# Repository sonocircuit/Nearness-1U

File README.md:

# Nearness-1U

This is an adaption of [sarnesjo's nearness module](https://github.com/sarnesjo/nearness) in 1U Pulplogic format.

### Changes made:

- New layout and format. All parts fit on a single 2-layer PCB.
- Added a second input for the center position (50:50) instead of one.
- Added a 3pin link header to connect the outputs directly to an EXI[S]T module. Pluging a cable into the output jacks breaks the connection.

## Make your own

[Eagle files](https://github.com/sonoCircuits/Nearness-1U/tree/master/NEARNESS%201U%20EAGLE%20FILES)

[Octopart BOM](https://octopart.com/bom-tool/OzYDJwBg)

## Licence

Thanks to sarnesjo for sharing! Same licence applies.

[CC BY-SA 4.0](http://creativecommons.org/licenses/by-sa/4.0/)

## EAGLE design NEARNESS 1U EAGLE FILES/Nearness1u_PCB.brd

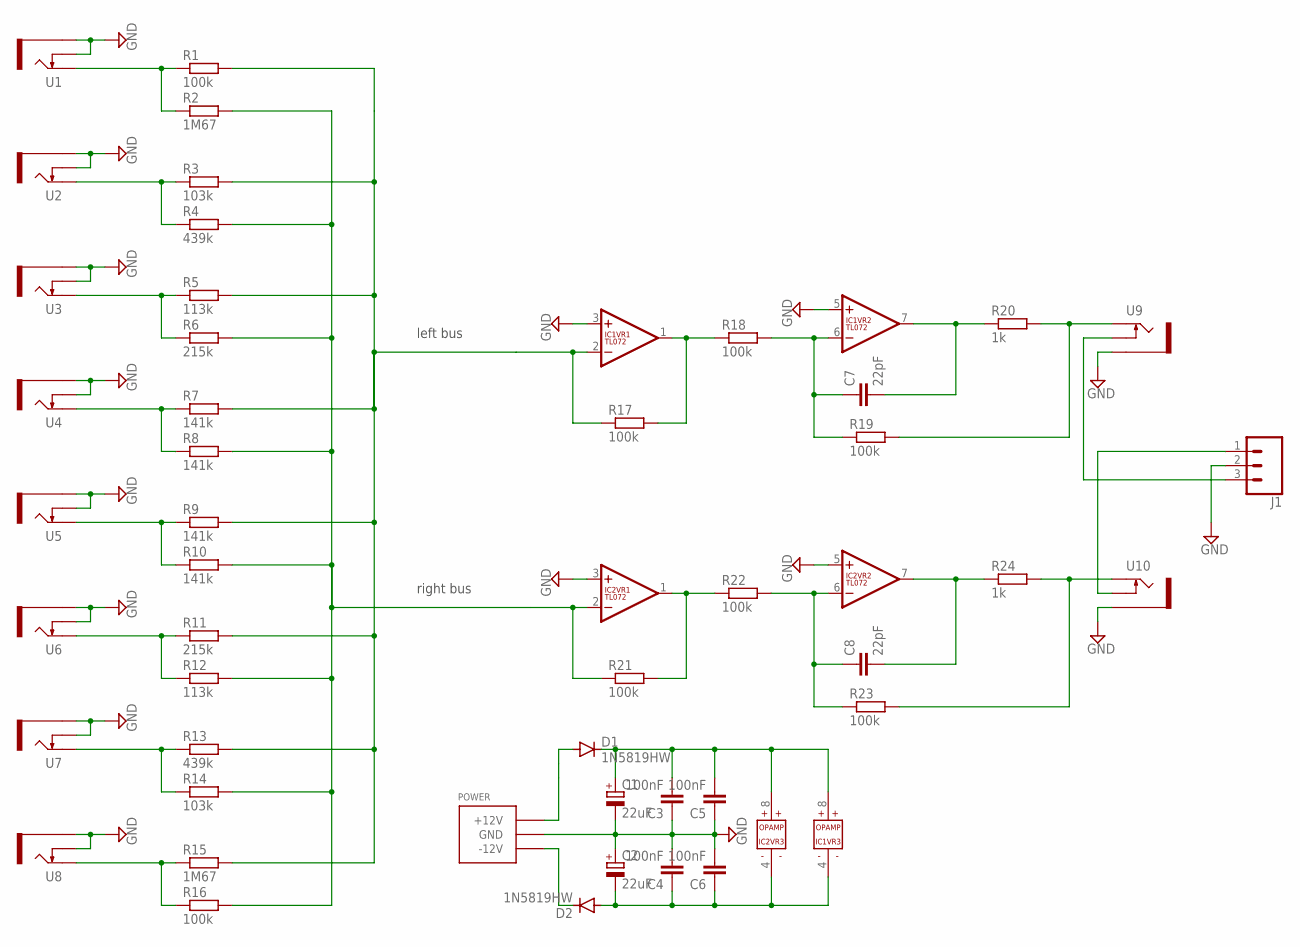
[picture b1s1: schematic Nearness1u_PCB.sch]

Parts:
C1, C2: 22uF; 153CLV-0405
C3, C4, C5, C6: 100nF; C0805
C7, C8: 22pF; C0805
D1, D2: 1N5819HW; SOD123
IC1, IC2: TL072; SO08
J1: CONN_03; 1X03
POWER: POWER_SIMPLE; 2X05_SMT_HEADER
R1, R16, R17, R18, R19, R21, R22, R23: 100k; R0805
R2, R15: 1M67; R0805
R3, R14: 103k; R0805
R4, R13: 439k; R0805
R5, R12: 113k; R0805
R6, R11: 215k; R0805
R7, R8, R9, R10: 141k; R0805
R20, R24: 1k; R0805
U1, U2, U3, U4, U5, U6, U7, U8, U9, U10: THONKICONNNEW; WQP-PJ301M-12_JACK

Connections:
GND: C1.-, C2.+, C3.1, C4.2, C5.1, C6.2, IC1.3 (+IN), IC1.5 (+IN), IC2.3 (+IN), IC2.5 (+IN), J1.2, POWER.3 (GND), POWER.4 (GND), POWER.5 (GND), POWER.6 (GND), POWER.7 (GND), POWER.8 (GND), U1.P$2_SWITCH (SWITCH), U1.P$3_SLEEVE (SLEEVE), U2.P$2_SWITCH (SWITCH), U2.P$3_SLEEVE (SLEEVE), U3.P$2_SWITCH (SWITCH), U3.P$3_SLEEVE (SLEEVE), U4.P$2_SWITCH (SWITCH), U4.P$3_SLEEVE (SLEEVE), U5.P$2_SWITCH (SWITCH), U5.P$3_SLEEVE (SLEEVE), U6.P$2_SWITCH (SWITCH), U6.P$3_SLEEVE (SLEEVE), U7.P$2_SWITCH (SWITCH), U7.P$3_SLEEVE (SLEEVE), U8.P$2_SWITCH (SWITCH), U8.P$3_SLEEVE (SLEEVE), U9.P$3_SLEEVE (SLEEVE), U10.P$3_SLEEVE (SLEEVE)
LEFT_BUS: IC1.2 (-IN), R1.2, R3.2, R5.2, R7.2, R9.2, R11.2, R13.2, R15.2, R17.1
unnamed: R1.1, R2.1, U1.P$1_TIP (TIP)
unnamed: IC2.1 (OUT), R21.2, R22.1
unnamed: C8.1, IC2.6 (-IN), R22.2, R23.1
unnamed: IC1.1 (OUT), R17.2, R18.1
unnamed: R3.1, R4.1, U2.P$1_TIP (TIP)
unnamed: C7.1, IC1.6 (-IN), R18.2, R19.1
unnamed: C7.2, IC1.7 (OUT), R20.1
unnamed: R5.1, R6.1, U3.P$1_TIP (TIP)
unnamed: C8.2, IC2.7 (OUT), R24.1
unnamed: R19.2, R20.2, U9.P$1_TIP (TIP)
unnamed: R7.1, R8.1, U4.P$1_TIP (TIP)
unnamed: R23.2, R24.2, U10.P$1_TIP (TIP)
unnamed: R9.1, R10.1, U5.P$1_TIP (TIP)
unnamed: D1.A, POWER.9 (+12V), POWER.10 (+12V)
unnamed: D2.C, POWER.1 (-12V), POWER.2 (-12V)
unnamed: R11.1, R12.1, U6.P$1_TIP (TIP)
unnamed: J1.3, U9.P$2_SWITCH (SWITCH)
unnamed: R13.1, R14.1, U7.P$1_TIP (TIP)
unnamed: J1.1, U10.P$2_SWITCH (SWITCH)
unnamed: R15.1, R16.1, U8.P$1_TIP (TIP)
RIGHT_BUS: IC2.2 (-IN), R2.2, R4.2, R6.2, R8.2, R10.2, R12.2, R14.2, R16.2, R21.1
V+: C1.+, C3.2, C5.2, D1.C, IC1.8 (V+), IC2.8 (V+)
V-: C2.-, C4.1, C6.1, D2.A, IC1.4 (V-), IC2.4 (V-)

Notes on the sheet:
left bus
right bus

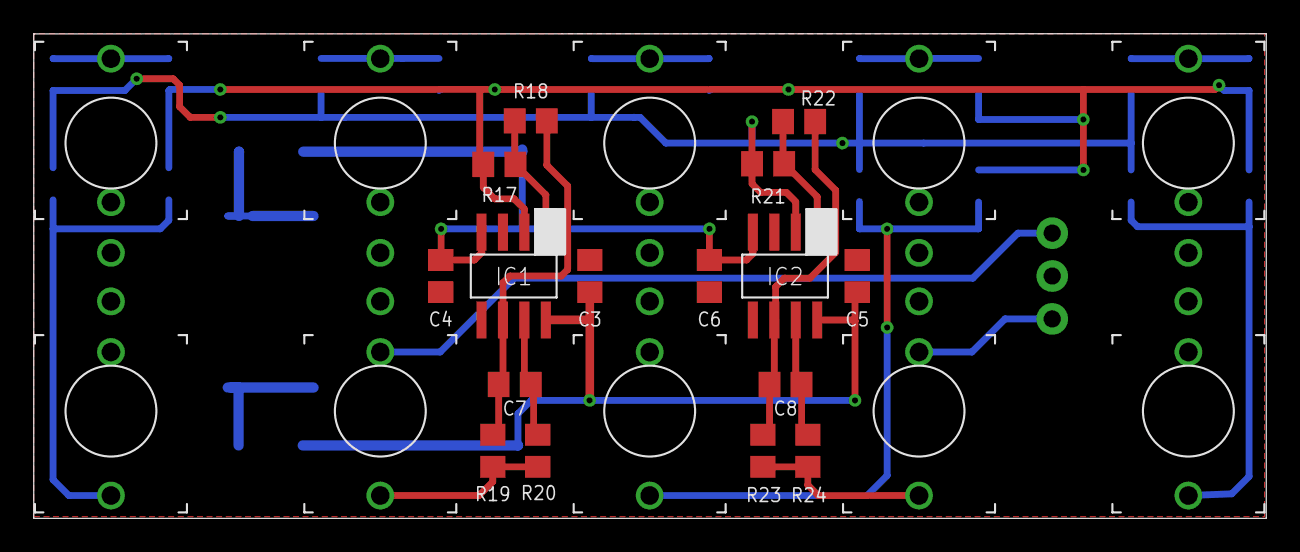
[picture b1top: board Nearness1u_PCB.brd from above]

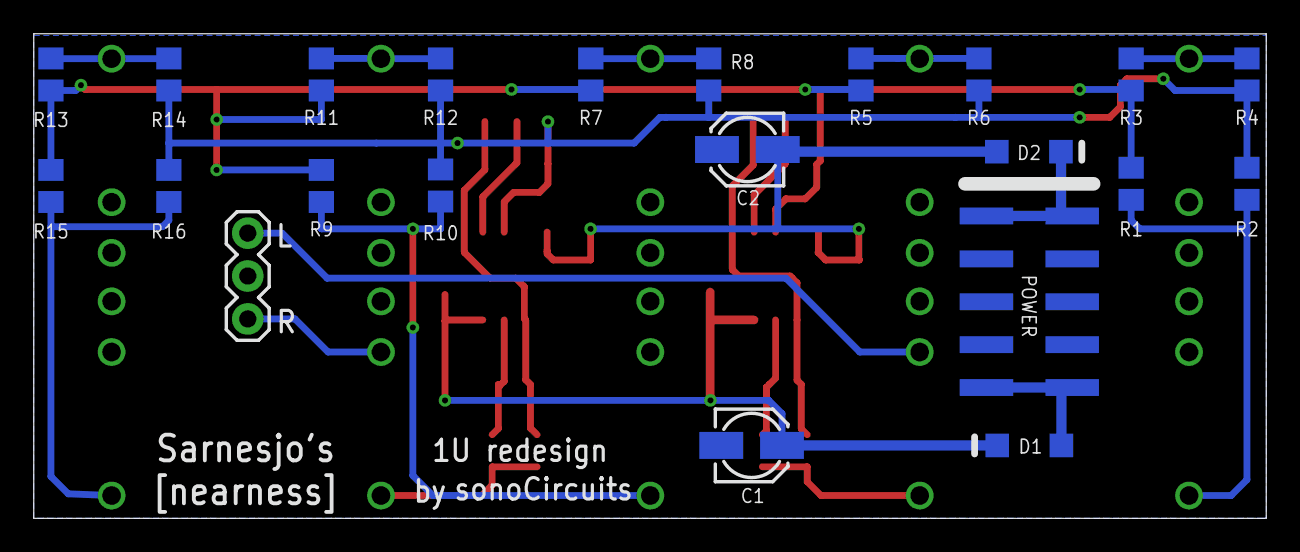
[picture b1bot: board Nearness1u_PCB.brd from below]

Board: 2 copper layers, 73.0 x 28.7 mm, 48 parts (22 on the bottom side), 25 nets.

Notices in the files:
parts and their libraries:
SparkFun-Connectors: Licensing: Creative Commons ShareAlike 4.0 International - https://creativecommons.org/licenses/by-sa/4.0
